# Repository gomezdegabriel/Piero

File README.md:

# Piero
This is and Educational Project developped Mechatronics and Robotics Teaching.

Design: 

Programming:

Acknowledgments:

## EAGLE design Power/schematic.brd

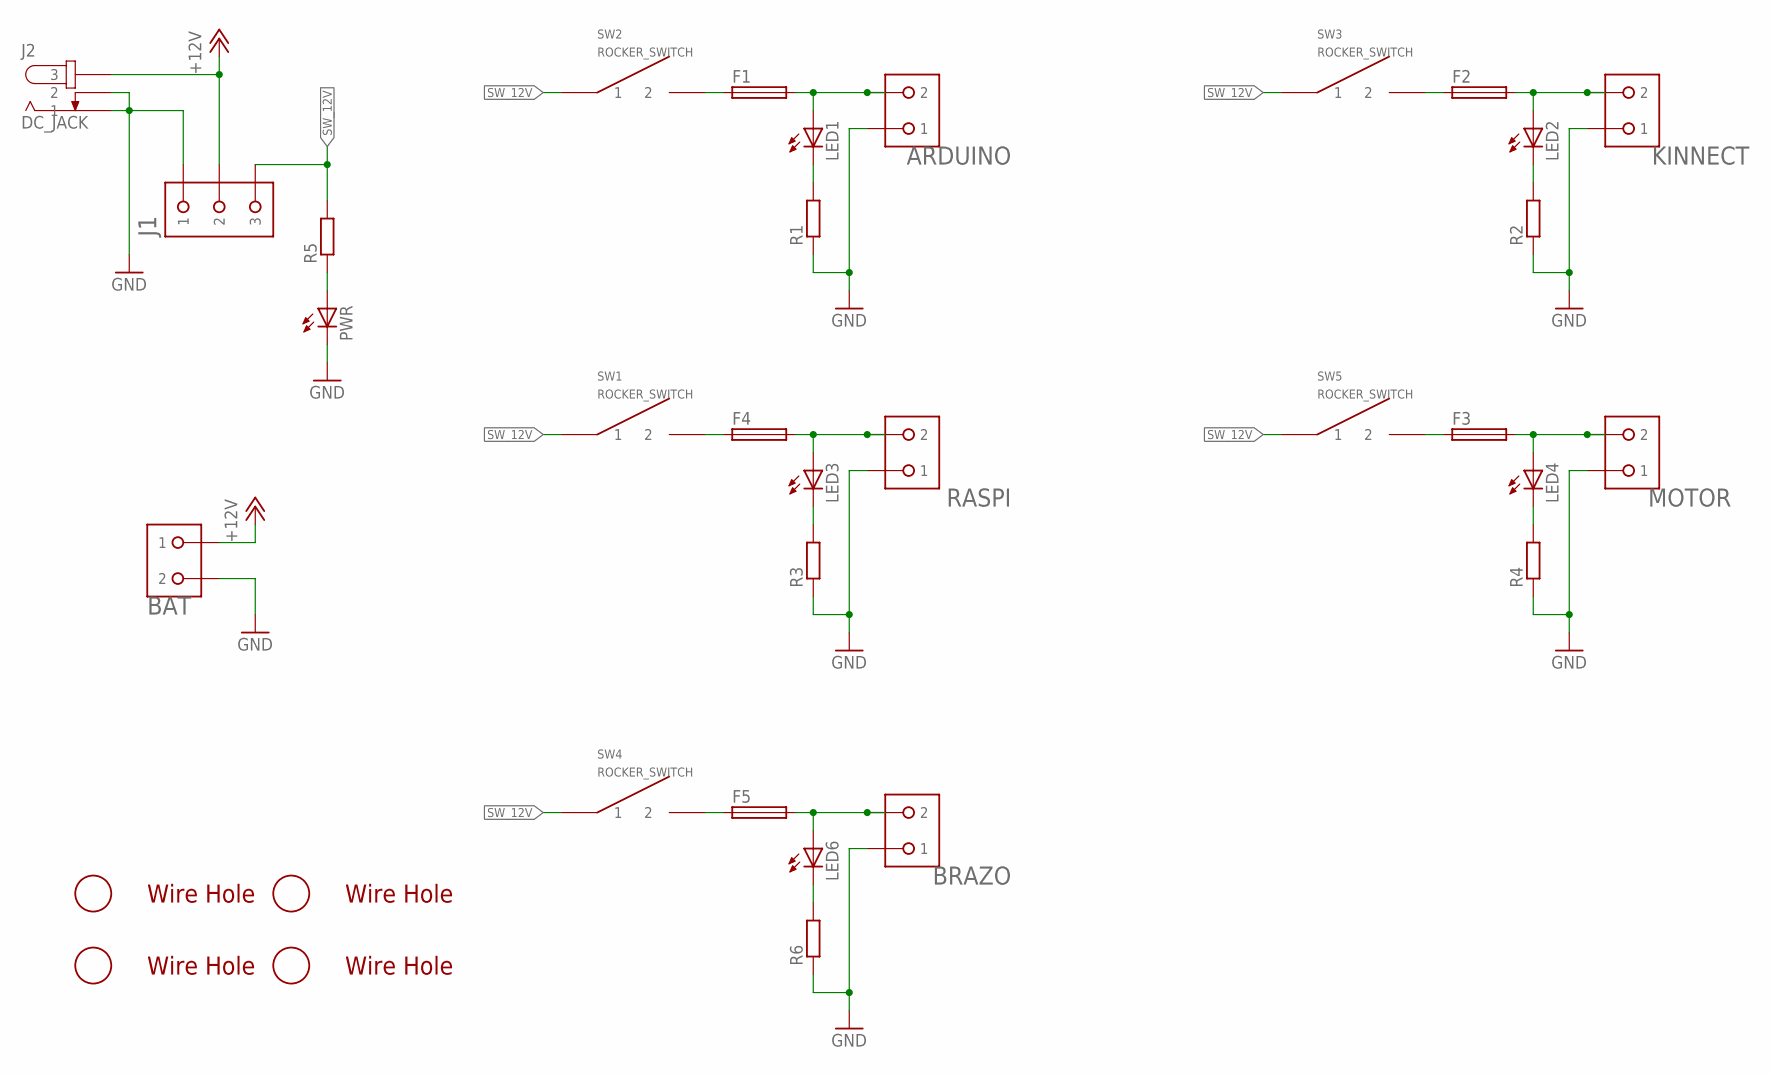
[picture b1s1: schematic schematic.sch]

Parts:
ARDUINO: B2P-VH(LF)(SN); B2P
BAT: B2P-VH(LF)(SN); B2P
BRAZO: B2P-VH(LF)(SN); B2P
F1, F2, F3, F4, F5: FUSETE5; TE5
J1: B3P-VH
J2: DC_JACK
KINNECT: B2P-VH(LF)(SN); B2P
LED1, LED2, LED3, LED4, LED6: LEDCHIP-LED0805; CHIP-LED0805
MOTOR: B2P-VH(LF)(SN); B2P
PWR: LED3MM
R1, R2, R3, R4, R5, R6: R-EU_R0805; R0805
RASPI: B2P-VH(LF)(SN); B2P
SW1, SW2, SW3, SW4, SW5: ROCKER_SWITCH
U$1, U$3, U$4, U$5: 3MMHOLE

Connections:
+12V: BAT.1, J1.2, J2.2 (3), J2.8 (3), J2.9 (3)
GND: ARDUINO.1, BAT.2, BRAZO.1, J1.1, J2.1 (2), J2.3 (1), J2.4 (2), J2.5 (2), J2.6 (1), J2.7 (1), KINNECT.1, MOTOR.1, PWR.K (C), R1.1, R2.1, R3.1, R4.1, R6.1, RASPI.1
unnamed: ARDUINO.2, F1.2, LED1.A
unnamed: LED1.C, R1.2
unnamed: F2.2, KINNECT.2, LED2.A
unnamed: F4.2, LED3.A, RASPI.2
unnamed: LED2.C, R2.2
unnamed: F3.2, LED4.A, MOTOR.2
unnamed: F1.1, SW2.P$12 (2), SW2.P$13 (2), SW2.P$14 (2), SW2.P$15 (2), SW2.P$16 (2), SW2.P$17 (2), SW2.P$18 (2), SW2.P$19 (2), SW2.P$20 (2), SW2.P$21 (2), SW2.P$22 (2)
unnamed: F4.1, SW1.P$12 (2), SW1.P$13 (2), SW1.P$14 (2), SW1.P$15 (2), SW1.P$16 (2), SW1.P$17 (2), SW1.P$18 (2), SW1.P$19 (2), SW1.P$20 (2), SW1.P$21 (2), SW1.P$22 (2)
unnamed: F3.1, SW5.P$12 (2), SW5.P$13 (2), SW5.P$14 (2), SW5.P$15 (2), SW5.P$16 (2), SW5.P$17 (2), SW5.P$18 (2), SW5.P$19 (2), SW5.P$20 (2), SW5.P$21 (2), SW5.P$22 (2)
unnamed: F2.1, SW3.P$12 (2), SW3.P$13 (2), SW3.P$14 (2), SW3.P$15 (2), SW3.P$16 (2), SW3.P$17 (2), SW3.P$18 (2), SW3.P$19 (2), SW3.P$20 (2), SW3.P$21 (2), SW3.P$22 (2)
unnamed: LED4.C, R4.2
unnamed: PWR.A, R5.1
unnamed: BRAZO.2, F5.2, LED6.A
unnamed: F5.1, SW4.P$12 (2), SW4.P$13 (2), SW4.P$14 (2), SW4.P$15 (2), SW4.P$16 (2), SW4.P$17 (2), SW4.P$18 (2), SW4.P$19 (2), SW4.P$20 (2), SW4.P$21 (2), SW4.P$22 (2)
unnamed: LED3.C, R3.2
unnamed: LED6.C, R6.2
SW_12V: J1.3, R5.2, SW1.P$1 (1), SW1.P$2 (1), SW1.P$3 (1), SW1.P$4 (1), SW1.P$5 (1), SW1.P$6 (1), SW1.P$7 (1), SW1.P$8 (1), SW1.P$9 (1), SW1.P$10 (1), SW1.P$11 (1), SW2.P$1 (1), SW2.P$2 (1), SW2.P$3 (1), SW2.P$4 (1), SW2.P$5 (1), SW2.P$6 (1), SW2.P$7 (1), SW2.P$8 (1), SW2.P$9 (1), SW2.P$10 (1), SW2.P$11 (1), SW3.P$1 (1), SW3.P$2 (1), SW3.P$3 (1), SW3.P$4 (1), SW3.P$5 (1), SW3.P$6 (1), SW3.P$7 (1), SW3.P$8 (1), SW3.P$9 (1), SW3.P$10 (1), SW3.P$11 (1), SW4.P$1 (1), SW4.P$2 (1), SW4.P$3 (1), SW4.P$4 (1), SW4.P$5 (1), SW4.P$6 (1), SW4.P$7 (1), SW4.P$8 (1), SW4.P$9 (1), SW4.P$10 (1), SW4.P$11 (1), SW5.P$1 (1), SW5.P$2 (1), SW5.P$3 (1), SW5.P$4 (1), SW5.P$5 (1), SW5.P$6 (1), SW5.P$7 (1), SW5.P$8 (1), SW5.P$9 (1), SW5.P$10 (1), SW5.P$11 (1)

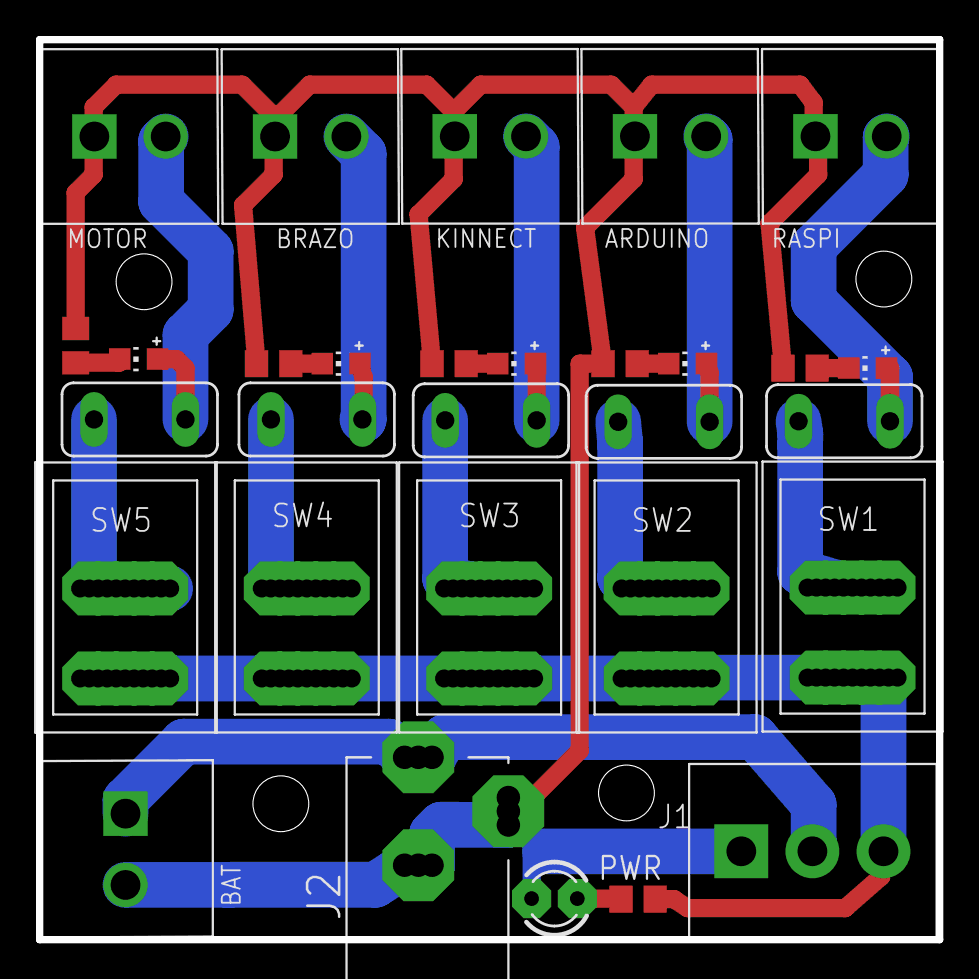
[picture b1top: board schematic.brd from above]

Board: 2 copper layers, 50.0 x 50.0 mm, 34 parts (0 on the bottom side), 19 nets.

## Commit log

2015-03-05 :octocat: Added .gitattributes & .gitignore files
2015-03-05 Added design files
2015-03-05 Added other files
2015-03-07 Initial rearrangements
